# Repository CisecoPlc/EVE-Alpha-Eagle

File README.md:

EVE-Alpha-Eagle
===============

Eagle files for the EVE Alpha Board

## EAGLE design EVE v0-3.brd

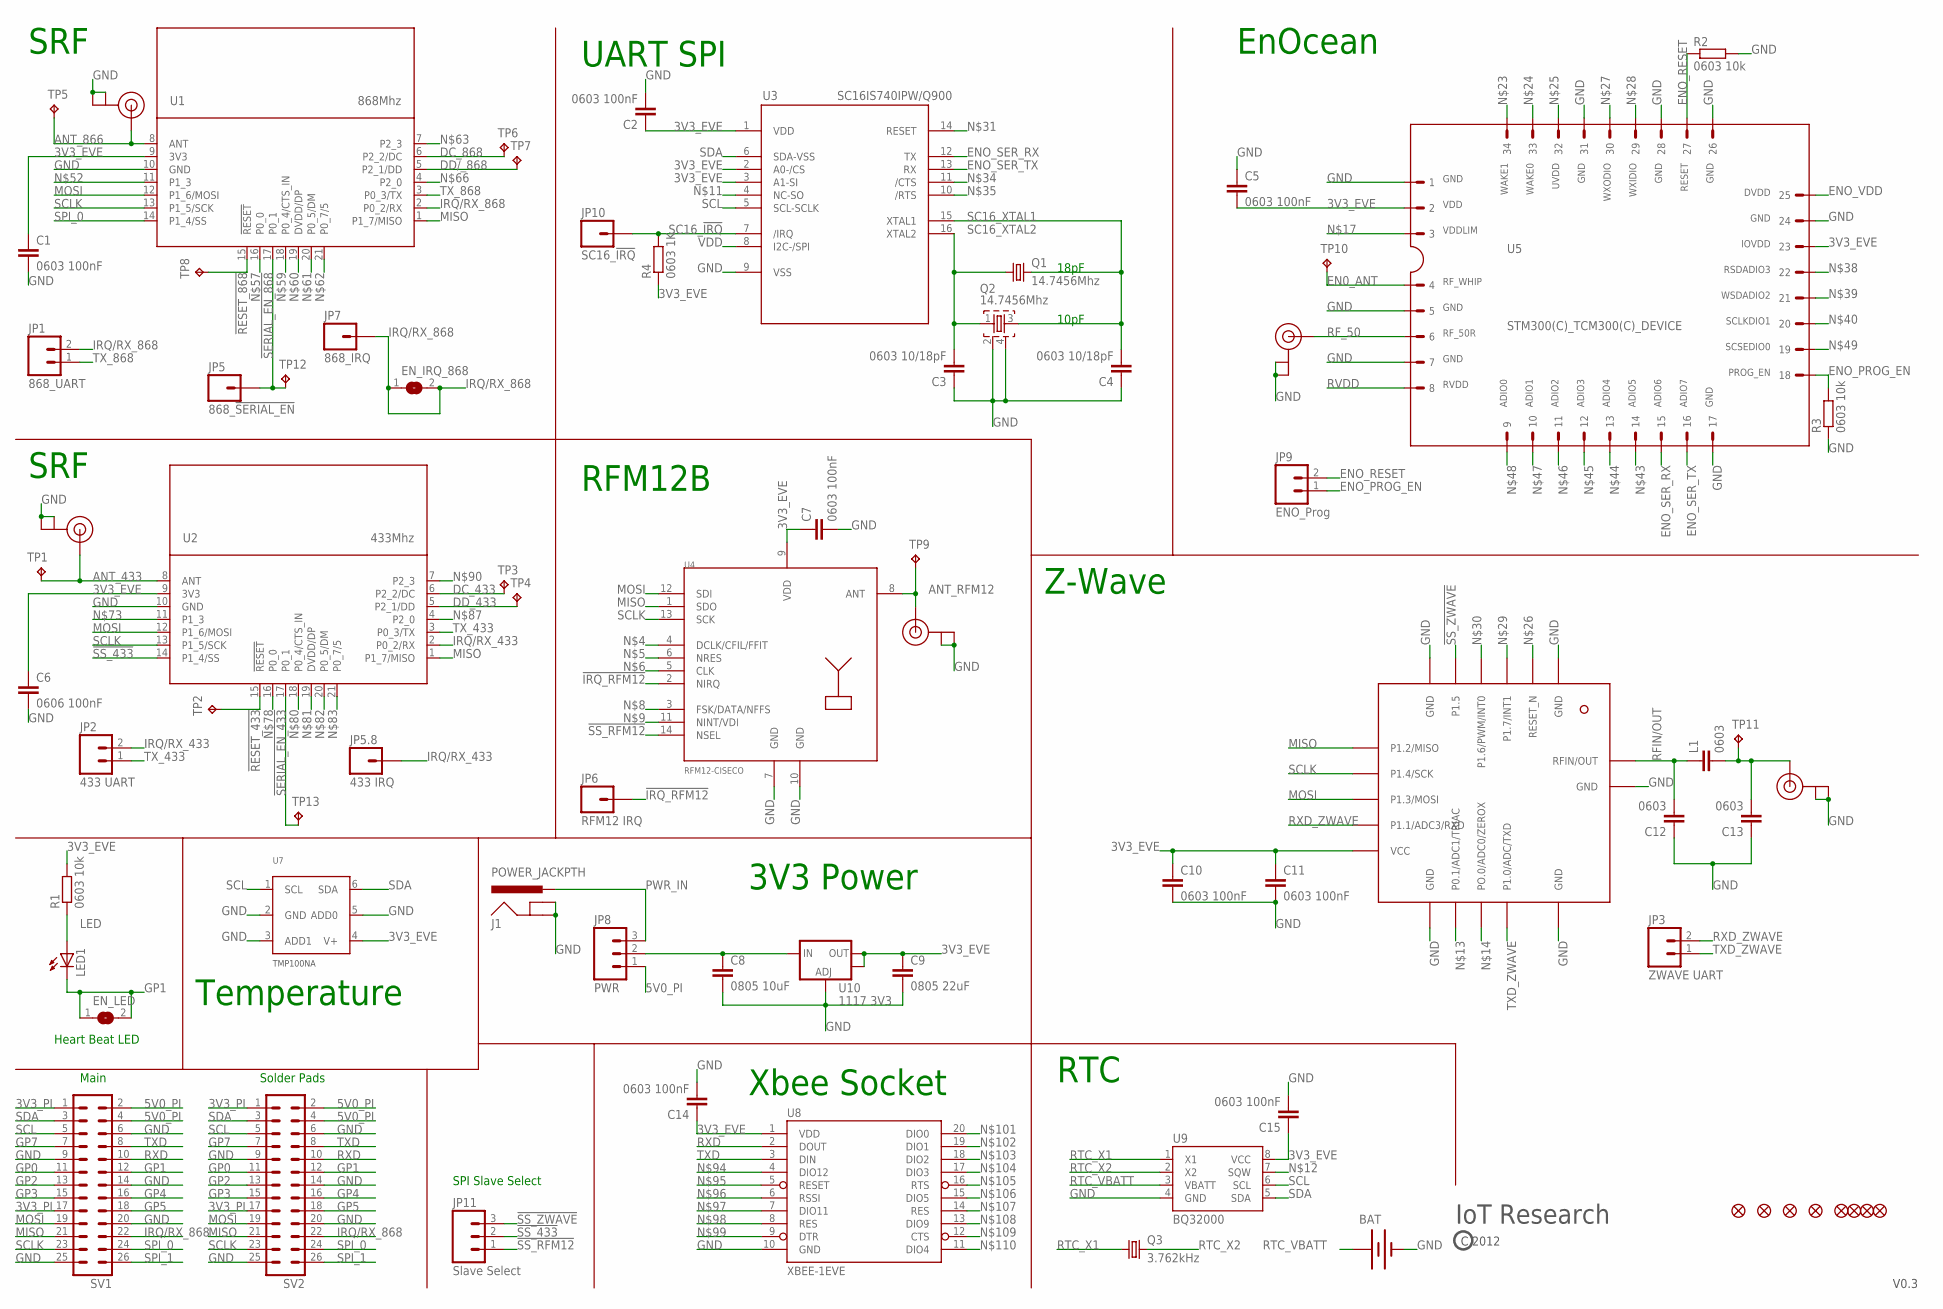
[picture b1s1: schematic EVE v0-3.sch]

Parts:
BAT: BATTERY12MM-BK-855; BATTCON_12MM-BK-885
C1, C2, C5, C7, C10, C11, C14, C15: 0603 100nF; C0603K-SMALL
C3, C4: 0603 10/18pF; C0603K-SMALL
C6: 0606 100nF; C0603K-SMALL
C8: 0805 10uF; C0805
C9: 0805 22uF; C0805
C12, C13: 0603; C0603K-SMALL
EN_IRQ_868: SJ
EN_LED: SJ
J1: POWER_JACKPTH; POWER_JACK_PTH
JP1: 868_UART; 1X02_NO_SILK
JP2: 433 UART; 1X02_NO_SILK
JP3: ZWAVE UART; 1X02_NO_SILK
JP4, JP12, JP13, JP14, JP15, JP16, JP17, JP18: FIDUCIAL1X2-STOP; FIDUCIAL-1X2-STOP
JP5: 868_!SERIAL_EN; 1X01NS
JP5.8: 433 IRQ; 1X01NS
JP6: RFM12 IRQ; 1X01NS
JP7: 868_IRQ; 1X01NS
JP8: PWR; 1X03_NO_SILK
JP9: ENO_Prog; 1X02_NO_SILK
JP10: SC16_!IRQ; 1X01NS
JP11: Slave Select; 1X03_NO_SILK
L1: 0603; C0603K-SMALL
LED1: LEDREVERSE; LED-REVERSE
Q1: 14.7456Mhz; CRYSTAL-SMD-10.5X4.8-2PIN
Q2: 14.7456Mhz; CRYSTAL-SMD-ABM8G
Q3: 3.762kHz; MC-306
R1, R2, R3: 0603 10k; C0603K-SMALL
R4: 0603 1K; C0603K-SMALL
SV1: MA13-2-NO-SILK; MA13-2-NS
SV2: MA13-2
TP1, TP5, TP9, TP10, TP11: TPPAD1-13; P1-13
TP2, TP3, TP4, TP6, TP7, TP8, TP12, TP13: TPB1,27; B1,27
U1: 868Mhz; SRF-LANDING
U2: 433Mhz; SRF-LANDING-NO-ANT
U3: SC16IS740IPW/Q900; TSSOP-16
U4: RFM12-CISECO; RFM-CISECO
U5: STM300(C)_TCM300(C)_DEVICE; STM300(C)_TCM300(C)_FOOTPRINT
U6: ZWAVE-ZM3102N
U7: TMP100NA; SOT-23-6
U8: XBEE-1EVE; XBEE-EVE
U9: BQ32000; SO08
U10: 1117 3V3; SOT223
U11: U.FL 868; U.FL
U12: U.FL EnOcean; U.FL
U13: U.FL 433; U.FL
U14: U.FL RFM12B; U.FL
U15: U.FL Z-Wave; U.FL

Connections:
3V3_EVE: C1.1, C2.1, C5.2, C6.1, C7.1, C9.1, C10.1, C11.1, C14.1, C15.1, R1.2, R4.1, U1.9 (3V3), U2.9 (3V3), U3.1 (VDD), U3.2 (A0-/CS), U3.3 (A1-SI), U4.9 (VDD), U5.2, U5.23, U6.11 (VCC), U7.4 (V+), U8.1 (VDD), U9.8 (VCC), U10.2 (OUT), U10.4 (OUT)
3V3_PI: SV1.1, SV1.17, SV2.1, SV2.17
5V0_PI: JP8.1, SV1.2, SV1.4, SV2.2, SV2.4
!IRQ_RFM12: JP6.1, U4.2 (NIRQ)
!RESET_433: TP2.TP, U2.15 (!RESET)
!RESET_868: TP8.TP, U1.15 (!RESET)
!SERIAL_EN_433: TP13.TP, U2.17 (P0_1)
!SERIAL_EN_868: JP5.1, TP12.TP, U1.17 (P0_1)
!SS_433: JP11.2, U2.14 (P1_4/SS)
!SS_RFM12: JP11.1, U4.14 (NSEL)
!SS_ZWAVE: JP11.3, U6.5 (P1.5)
ANT_433: TP1.TP, U2.8 (ANT), U13.P$3 (SIGNAL)
ANT_866: TP5.TP, U1.8 (ANT), U11.P$3 (SIGNAL)
ANT_RFM12: TP9.TP, U4.8 (ANT), U14.P$3 (SIGNAL)
DC_433: TP3.TP, U2.6 (P2_2/DC)
DC_868: TP6.TP, U1.6 (P2_2/DC)
DD/_868: TP7.TP, U1.5 (P2_1/DD)
DD_433: TP4.TP, U2.5 (P2_1/DD)
EN0_ANT: TP10.TP, U5.4
ENO_PROG_EN: JP9.1, R3.2, U5.18
ENO_RESET: JP9.2, R2.1, U5.27
ENO_SER_RX: U3.12 (TX), U5.15
ENO_SER_TX: U3.13 (RX), U5.16
ENO_VDD: U5.25
GND: BAT.GND (-), C1.2, C2.2, C3.1, C4.1, C5.1, C6.2, C7.2, C8.2, C9.2, C10.2, C11.2, C12.1, C13.1, C14.2, C15.2, J1.GND, J1.GNDBREAK, Q2.2, Q2.4, R2.2, R3.1, SV1.6, SV1.9, SV1.14, SV1.20, SV1.25, SV2.6, SV2.9, SV2.14, SV2.20, SV2.25, U1.10 (GND), U2.10 (GND), U3.9 (VSS), U4.7 (GND), U4.10 (GND), U5.1, U5.5, U5.7, U5.17, U5.24, U5.26, U5.28, U5.31, U6.1 (GND), U6.6 (GND), U6.12 (GND), U6.16 (GND), U6.17 (GND), U7.2 (GND), U7.3 (ADD1), U7.5 (ADD0), U8.10 (GND), U9.4 (GND), U10.1 (ADJ), U11.P$1 (GND), U11.P$2 (GND), U12.P$1 (GND), U12.P$2 (GND), U13.P$1 (GND), U13.P$2 (GND), U14.P$1 (GND), U14.P$2 (GND), U15.P$1 (GND), U15.P$2 (GND)
GP0: SV1.11, SV2.11
GP1: EN_LED.1, EN_LED.2, LED1.C, SV1.12, SV2.12
GP2: SV1.13, SV2.13
GP3: SV1.15, SV2.15
GP4: SV1.16, SV2.16
GP5: SV1.18, SV2.18
GP7: SV1.7, SV2.7
IRQ/RX_433: JP2.2, JP5.8.1, U2.2 (P0_2/RX)
IRQ/RX_868: EN_IRQ_868.1, EN_IRQ_868.2, JP1.2, JP7.1, SV1.22, SV2.22, U1.2 (P0_2/RX)
LED: LED1.A, R1.1
MISO: SV1.21, SV2.21, U1.1 (P1_7/MISO), U2.1 (P1_7/MISO), U4.1 (SDO), U6.7 (P1.2/MISO)
MOSI: SV1.19, SV2.19, U1.12 (P1_6/MOSI), U2.12 (P1_6/MOSI), U4.12 (SDI), U6.9 (P1.3/MOSI)
unnamed: C13.2, L1.2, TP11.TP, U15.P$3 (SIGNAL)
PWR_IN: J1.PWR, JP8.3
RFIN/OUT: C12.2, L1.1, U6.18 (RFIN/OUT)
RF_50: U5.6, U12.P$3 (SIGNAL)
RTC_VBATT: BAT.PWR@2 (+), U9.3 (VBATT)
RTC_X1: Q3.1, U9.1 (X1)
RTC_X2: Q3.4 (2), U9.2 (X2)
RVDD: U5.8
RXD: SV1.10, SV2.10, U8.2 (DOUT)
RXD_ZWAVE: JP3.2, U6.10 (P1.1/ADC3/RXD)
SC16_!IRQ: JP10.1, R4.2, U3.7 (/IRQ)
SC16_XTAL1: C4.2, Q1.P$2 (2), Q2.3, U3.15 (XTAL1)
SC16_XTAL2: C3.2, Q1.P$1 (1), Q2.1, U3.16 (XTAL2)
SCL: SV1.5, SV2.5, U3.5 (SCL-SCLK), U7.1 (SCL), U9.6 (SCL)
SCLK: SV1.23, SV2.23, U1.13 (P1_5/SCK), U2.13 (P1_5/SCK), U4.13 (SCK), U6.8 (P1.4/SCK)
SDA: SV1.3, SV2.3, U3.6 (SDA-VSS), U7.6 (SDA), U9.5 (SDA)
SPI_0: SV1.24, SV2.24, U1.14 (P1_4/SS)
SPI_1: SV1.26, SV2.26
TXD: SV1.8, SV2.8, U8.3 (DIN)
TXD_ZWAVE: JP3.1, U6.15 (P1.0/ADC/TXD)
TX_433: JP2.1, U2.3 (P0_3/TX)
TX_868: JP1.1, U1.3 (P0_3/TX)
VCC_EVE: C8.1, JP8.2, U10.3 (IN)
VDD: U3.8 (I2C-/SPI)

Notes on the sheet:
Main
Solder Pads
V0.3
SRF
RTC
RFM12B
EnOcean
Z-Wave
Xbee Socket
Temperature
UART SPI
SPI Slave Select
Heart Beat LED
3V3 Power
18pF
10pF
IoT Research
C 2012

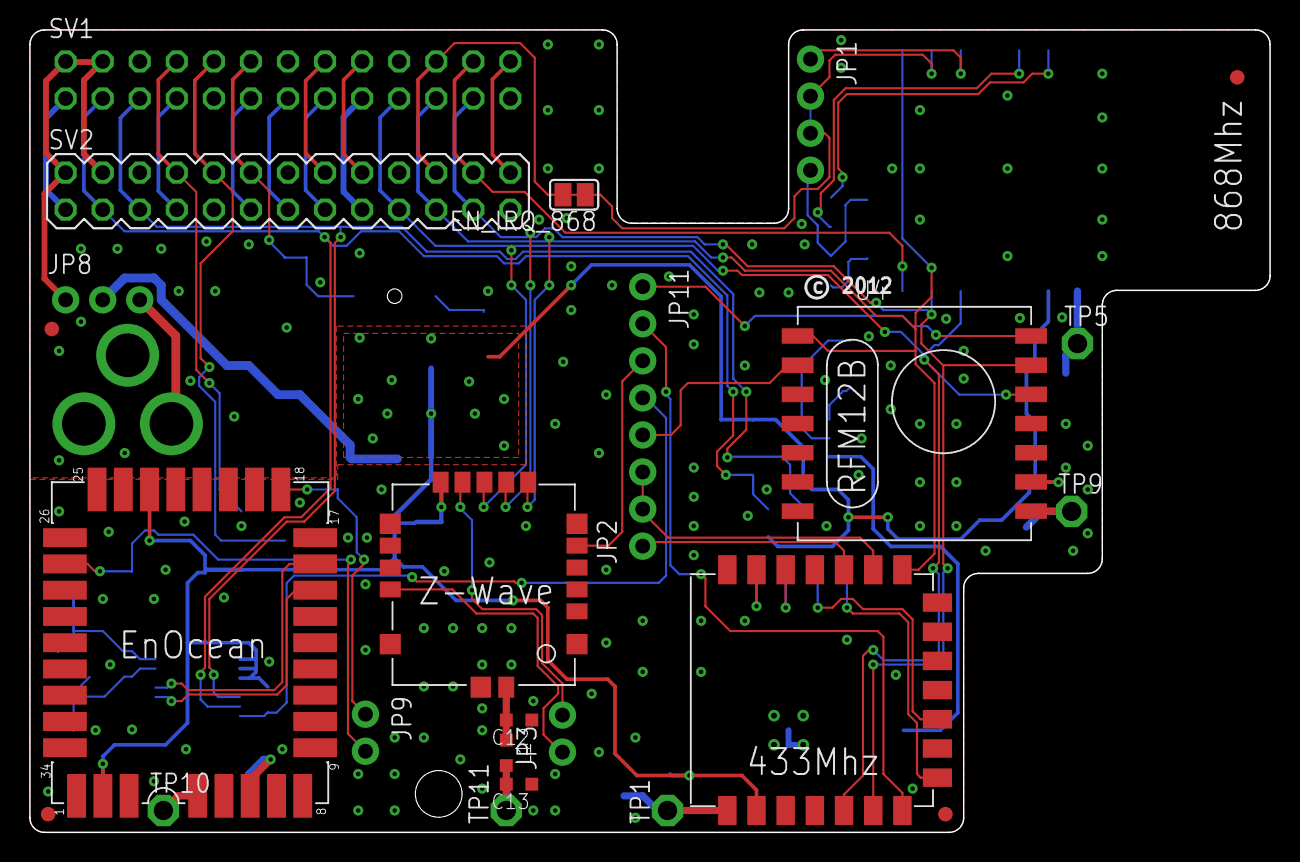
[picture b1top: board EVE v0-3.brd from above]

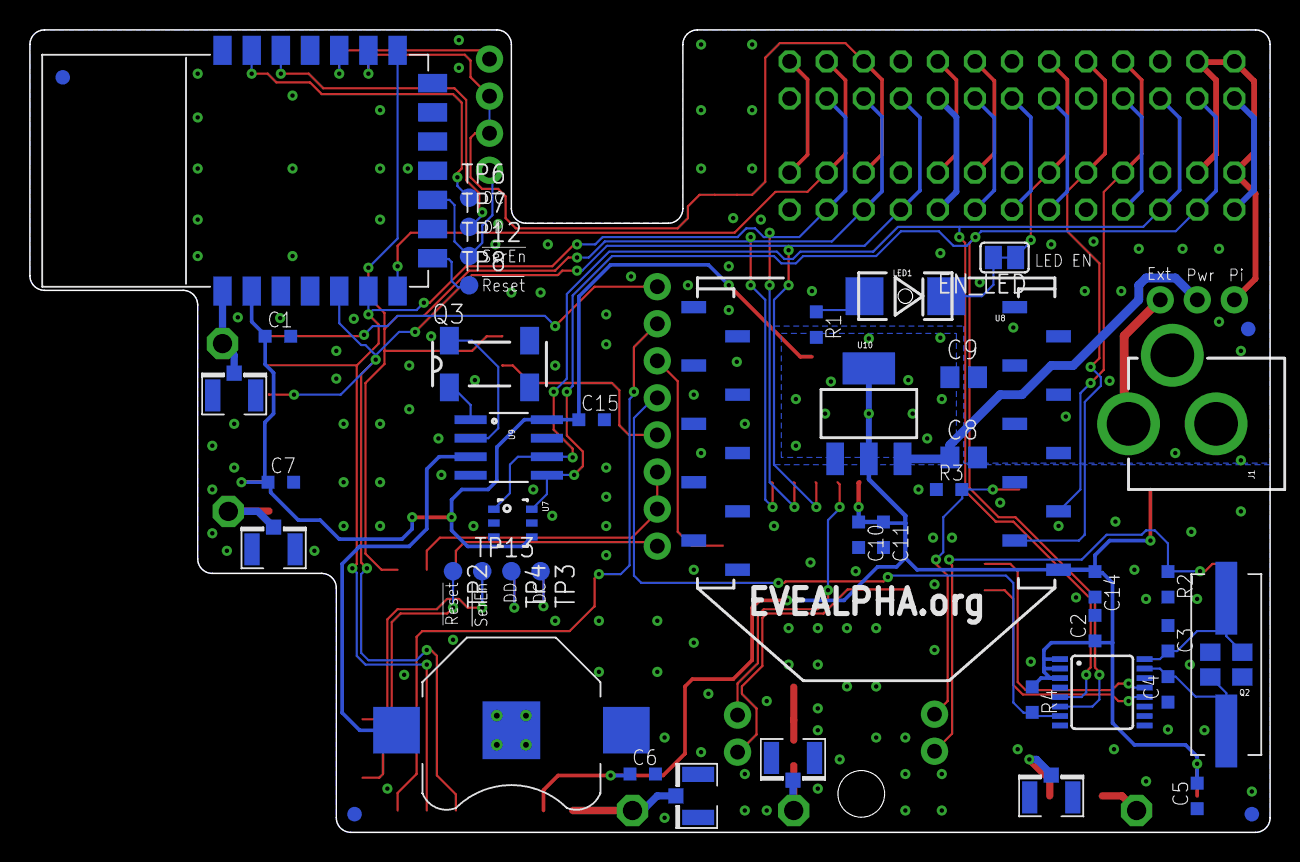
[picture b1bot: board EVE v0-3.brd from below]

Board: 2 copper layers, 85.0 x 55.0 mm, 78 parts (47 on the bottom side), 58 nets.

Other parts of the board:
U$8: EVE1

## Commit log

2012-12-03 EVE Alpha Eagle Files
2012-12-03 Adding PDF of Schematic and Board
